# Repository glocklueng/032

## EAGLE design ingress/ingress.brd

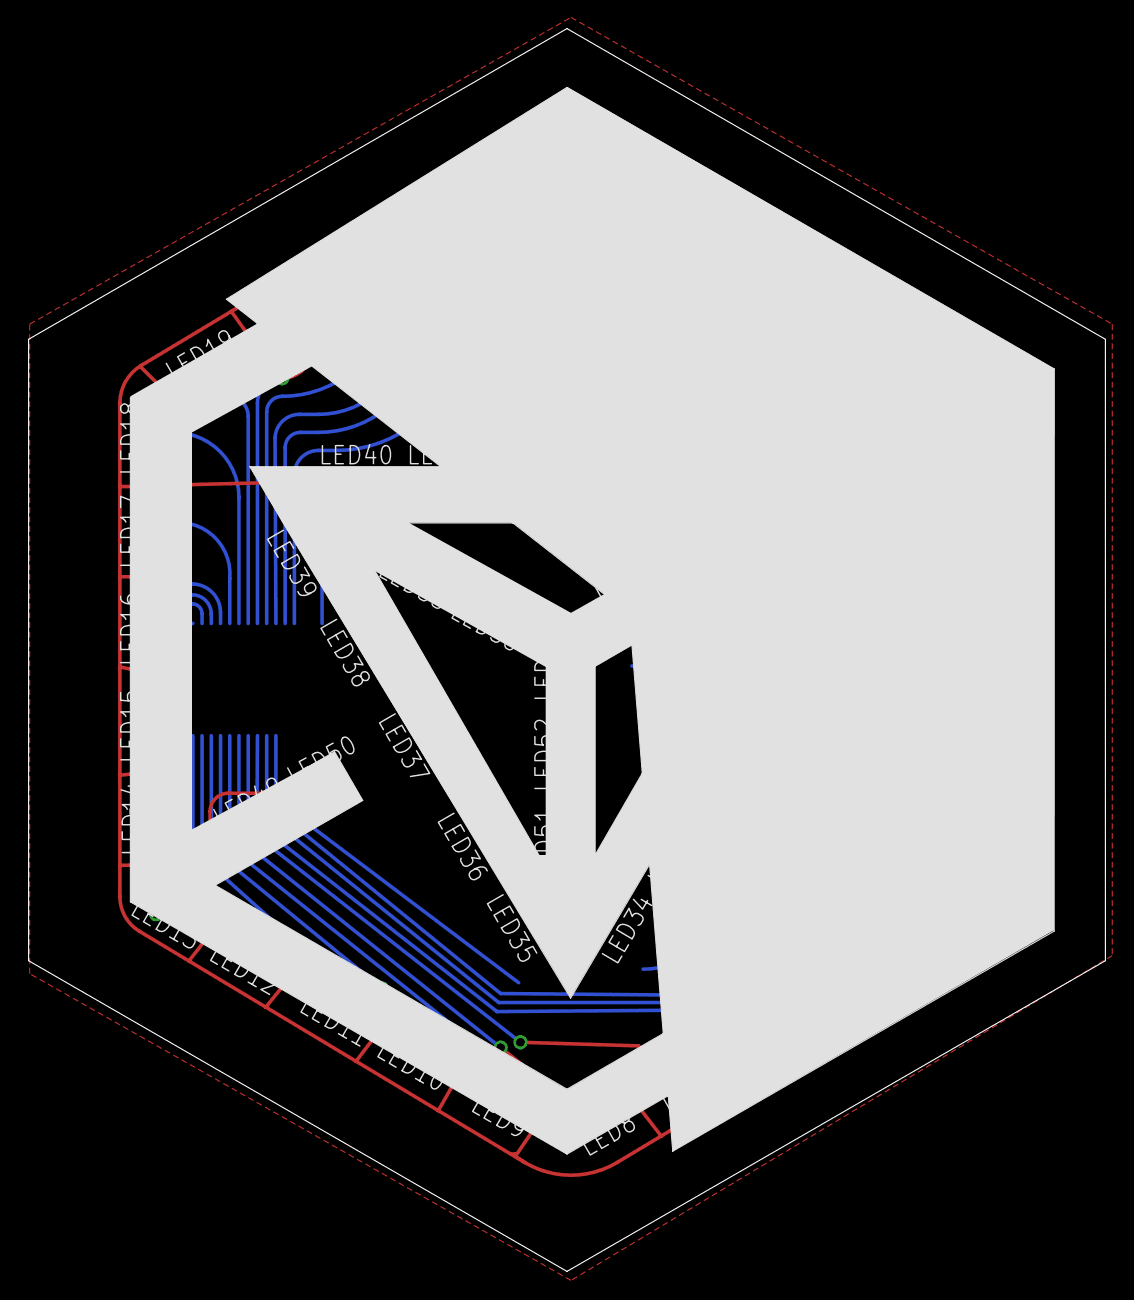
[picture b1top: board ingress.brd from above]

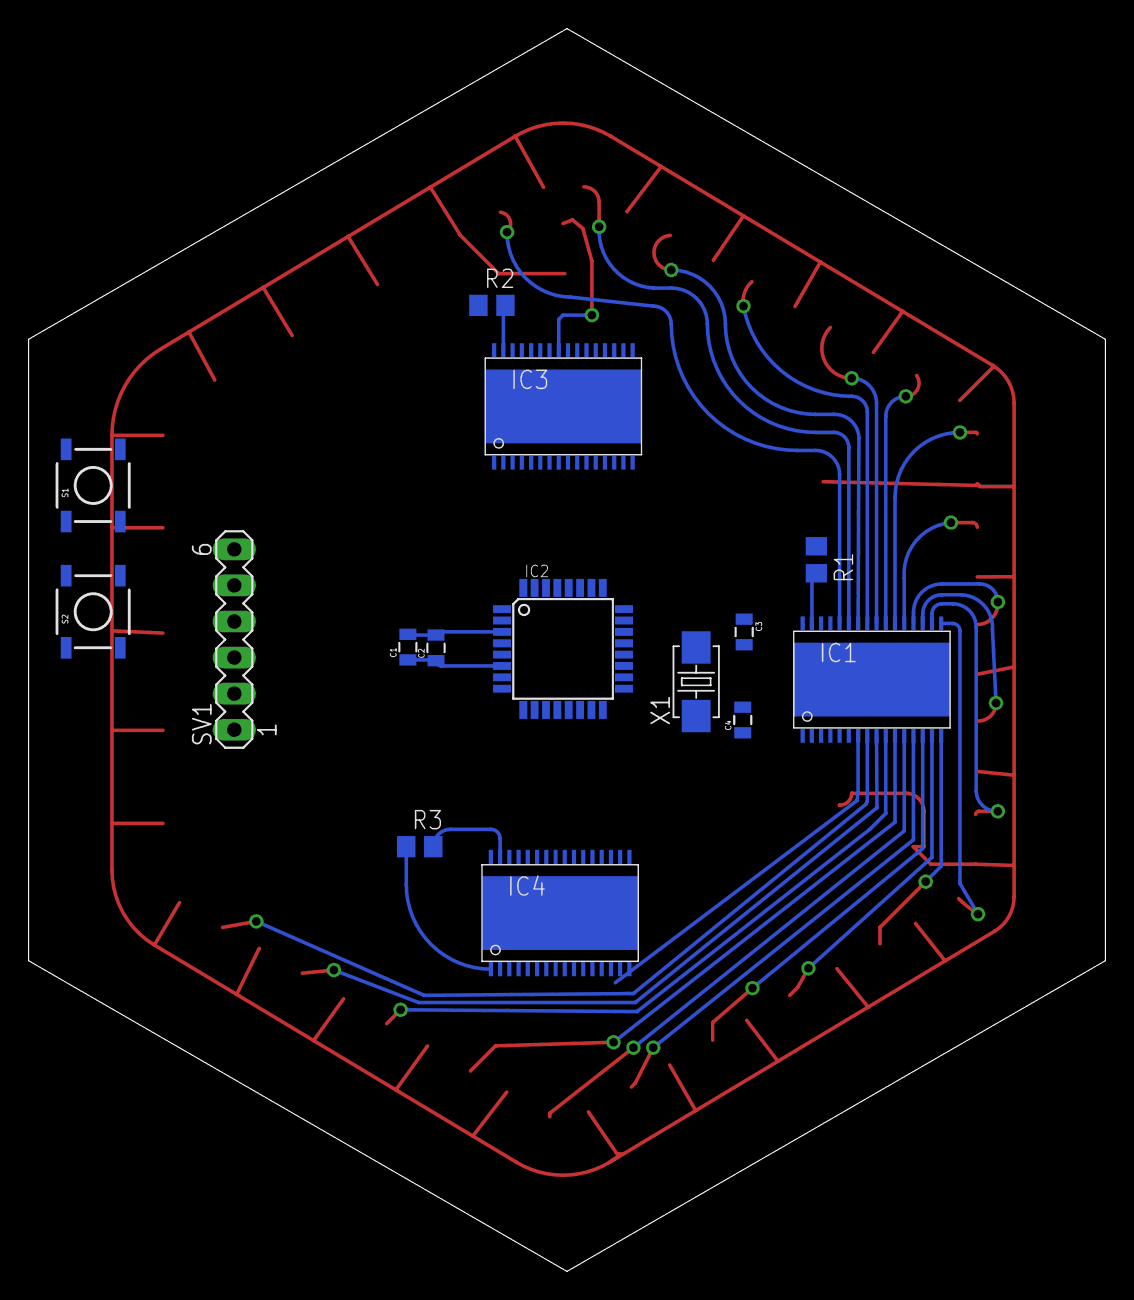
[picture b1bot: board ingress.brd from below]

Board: 2 copper layers, 75.8 x 87.5 mm, 74 parts (15 on the bottom side), 77 nets.

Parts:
C1, C2: .1uF; 0805
C3, C4: 18pF; 0805
IC1: HTSSOP32DAP
IC2: MEGA328-AI; TQFP32-08
IC3, IC4: SLICE_NOSHIFT_TLC5947HTSSOP32DAP; HTSSOP32DAP
LED1, LED2, LED3, LED4, LED5, LED6, LED7, LED8, LED9, LED10, LED11, LED12, LED13, LED14, LED15, LED16, LED17, LED18, LED19, LED20, LED21, LED22, LED23, LED24, LED25, LED26, LED27, LED28, LED29, LED30, LED31, LED32, LED33, LED34, LED35, LED36, LED37, LED38, LED39, LED40, LED41, LED42, LED43, LED44, LED45, LED46, LED47, LED48, LED49, LED50, LED51, LED52, LED53, LED54, LED55, LED56, LED57, LED58, LED59: CHIPLED_1206
R1, R2, R3: 20K; R0805
S1, S2: TACTILE_SWITCH_SMD
SV1: MA06-1
X1: 16Mhz; 5032

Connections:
BLANK: IC1.2, IC2.25, IC3.2, IC4.2
BUTTON: IC2.28, S2.3
COL1: IC1.5, LED1.C
COL2: IC1.6, LED2.C
COL3: IC1.7, LED3.C
COL4: IC1.8, LED4.C
COL5: IC1.9, LED5.C
COL6: IC1.10, LED6.C
COL7: IC1.11, LED7.C
COL8: IC1.12, LED8.C
COL9: IC1.13, LED9.C
COL10: IC1.14, LED10.C
COL11: IC1.15, LED11.C
COL12: IC1.16, LED12.C
COL13: IC1.17, LED13.C
COL14: IC1.18, LED14.C
COL15: IC1.19, LED15.C
COL16: IC1.20, LED16.C
COL17: IC1.21, LED17.C
COL18: IC1.22, LED18.C
COL19: IC1.23, LED19.C
COL20: IC1.24, LED20.C
COL21: IC1.25, LED21.C
COL22: IC1.26, LED22.C
COL23: IC1.27, LED23.C
COL24: IC1.28, LED24.C
COL25: IC3.5, LED25.C
COL26: IC3.6, LED26.C
COL27: IC3.7, LED27.C
COL28: IC3.8, LED28.C
COL29: IC3.9, LED29.C
COL30: IC3.10, LED30.C
COL31: IC3.11, LED31.C
COL32: IC3.12, LED32.C
COL33: IC3.13, LED33.C
COL34: IC3.14, LED34.C
COL35: IC3.15, LED35.C
COL36: IC3.16, LED36.C
COL37: IC3.17, LED37.C
COL38: IC3.18, LED38.C
COL39: IC3.19, LED39.C
COL40: IC3.20, LED40.C
COL41: IC3.21, LED41.C
COL42: IC3.22, LED42.C
COL43: IC3.23, LED43.C
COL44: IC3.24, LED44.C
COL45: IC3.25, LED45.C
COL46: IC3.26, LED46.C
COL47: IC3.27, LED47.C
COL48: IC3.28, LED48.C
COL49: IC4.5, LED49.C
COL50: IC4.6, LED50.C
COL51: IC4.7, LED51.C
COL52: IC4.8, LED52.C
COL53: IC4.9, LED53.C
COL54: IC4.10, LED54.C
COL55: IC4.11, LED55.C
COL56: IC4.12, LED56.C
COL57: IC4.13, LED57.C
COL58: IC4.14, LED58.C
COL59: IC4.15, LED59.C
GND: C1.2, C2.2, C3.2, C4.2, IC1.1, IC2.3, IC2.5, IC2.21, IC3.1, IC4.1, R1.1, R2.1, R3.1, S1.1, S1.2, S2.1, S2.2, SV1.6
MISO: IC2.16, SV1.2
MOSI: IC2.15, SV1.1
unnamed: IC3.31, R2.2
unnamed: C3.1, IC2.7, X1.2
unnamed: C4.1, IC2.8, X1.1
unnamed: IC1.31, R1.2
unnamed: IC4.31, R3.2
RST: IC2.29, S1.3, SV1.5
SCK: IC2.17, SV1.3
SCLK: IC1.3, IC2.24, IC3.3, IC4.3
SIN: IC1.4, IC2.23
SOUT: IC1.29, IC3.4
SOUT_2: IC3.29, IC4.4
VCC: C1.1, C2.1, IC1.32, IC2.4, IC2.6, IC2.18, IC2.20, IC3.32, IC4.32, LED1.A, LED2.A, LED3.A, LED4.A, LED5.A, LED6.A, LED7.A, LED8.A, LED9.A, LED10.A, LED11.A, LED12.A, LED13.A, LED14.A, LED15.A, LED16.A, LED17.A, LED18.A, LED19.A, LED20.A, LED21.A, LED22.A, LED23.A, LED24.A, LED25.A, LED26.A, LED27.A, LED28.A, LED29.A, LED30.A, LED31.A, LED32.A, LED33.A, LED34.A, LED35.A, LED36.A, LED37.A, LED38.A, LED39.A, LED40.A, LED41.A, LED42.A, LED43.A, LED44.A, LED45.A, LED46.A, LED47.A, LED48.A, LED49.A, LED50.A, LED51.A, LED52.A, LED53.A, LED54.A, LED55.A, LED56.A, LED57.A, LED58.A, LED59.A, SV1.4
XLAT: IC1.30, IC2.26, IC3.30, IC4.30

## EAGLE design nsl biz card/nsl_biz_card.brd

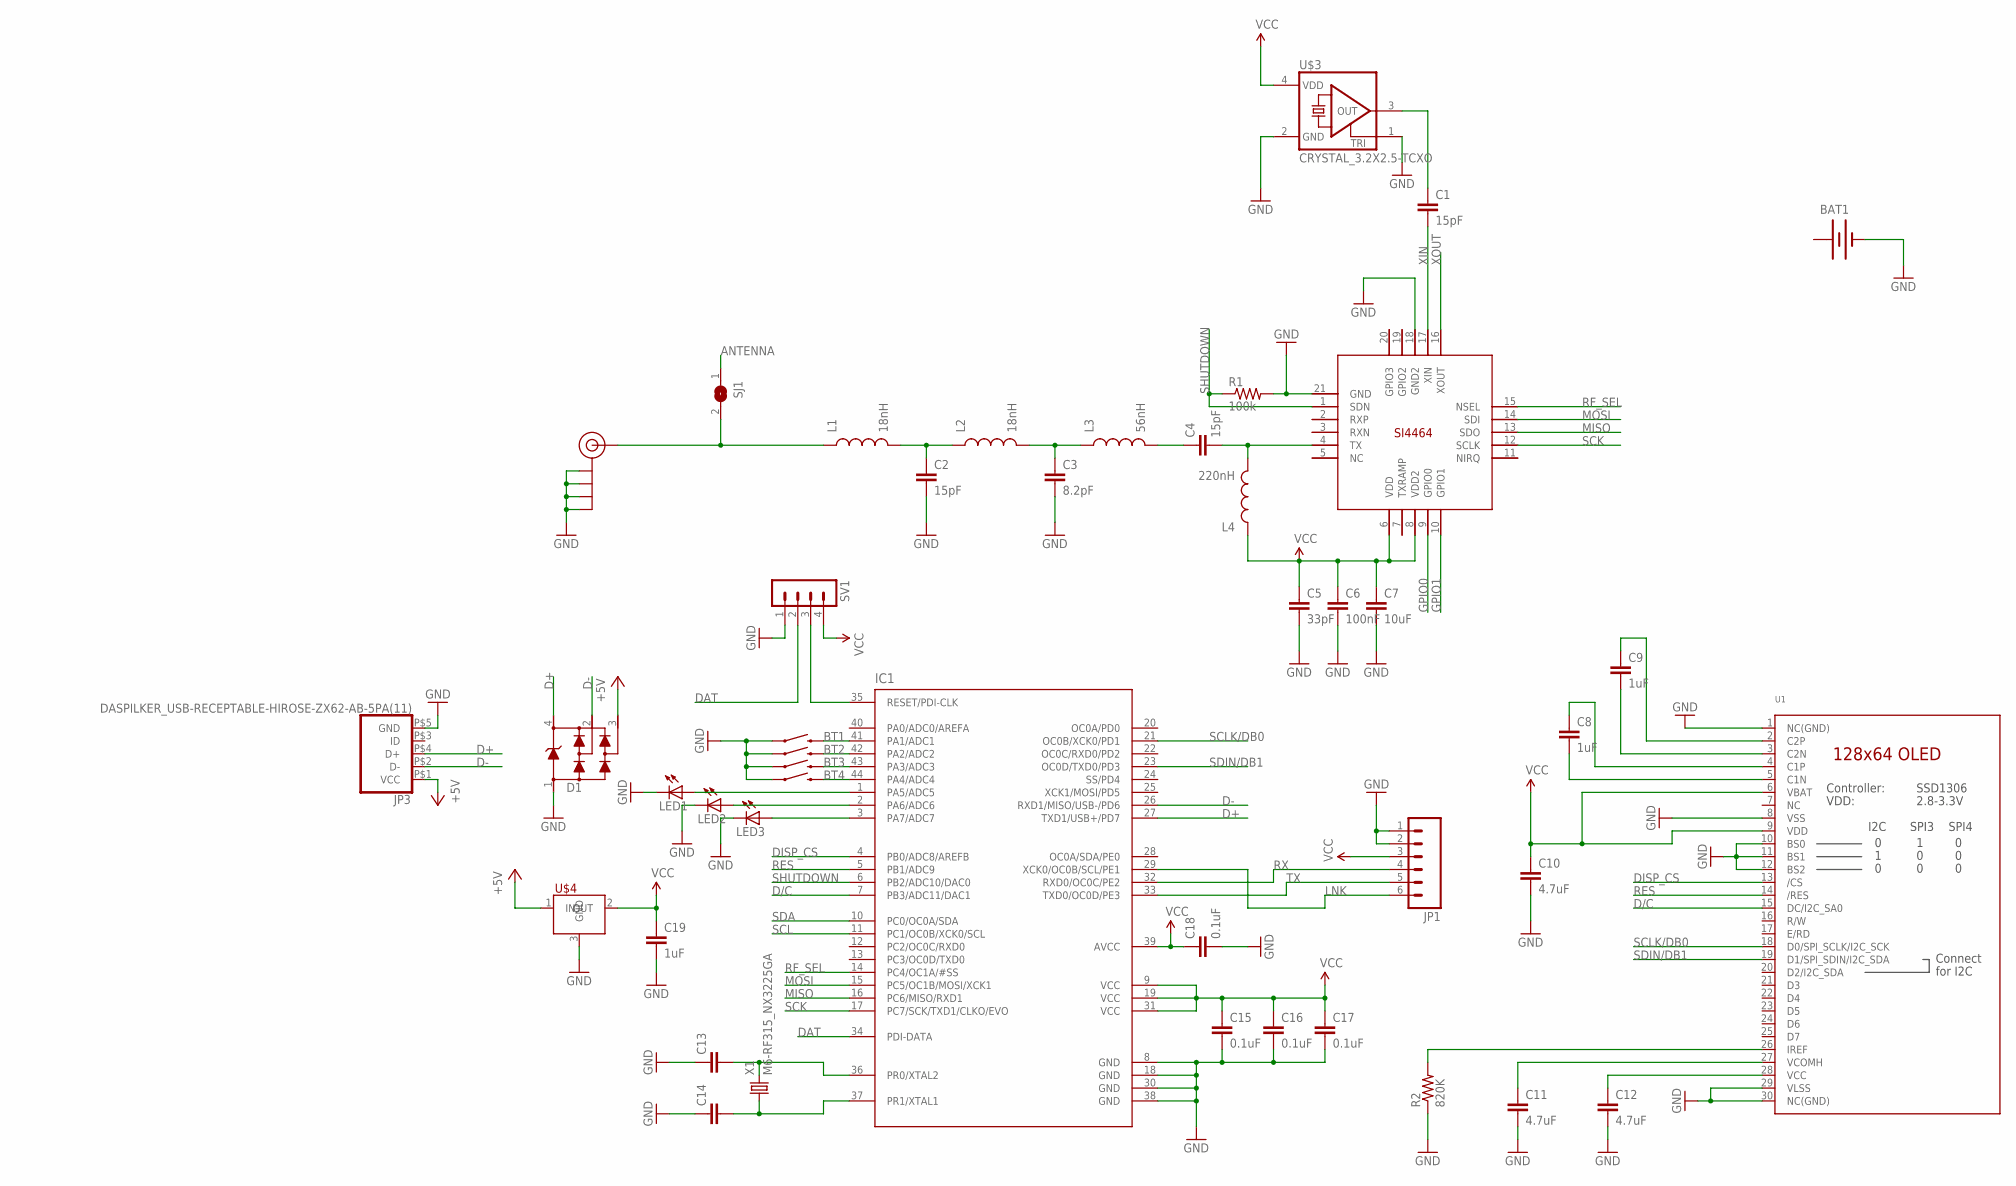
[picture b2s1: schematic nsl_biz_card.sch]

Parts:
BAT1: BATTERY12MM; BATTCON_12MM
C1, C2, C4: 15pF; 0603-CAP
C3: 8.2pF; 0603-CAP
C5: 33pF; 0603-CAP
C6: 100nF; 0603-CAP
C7: 10uF; 0603-CAP
C8, C9: 1uF; 0603-CAP
C10, C11, C12: 4.7uF; 0603-CAP
C13, C14: SPARKFUN_CAP0603-CAP; SPARKFUN_0603-CAP
C15, C16, C17, C18: 0.1uF; SPARKFUN_0603-CAP
C19: 1uF; SPARKFUN_0603-CAP
D1: USBUG_PRTR5V0U2X; USBUG_SOT143B
IC1: OUTLINE_NONOLITH_ATXMEGAXXA4U-AU; OUTLINE_NONOLITH_TQFP-44
J$1: SMA_EDGE; SMA-EDGE
JP1: M06SIP; 1X06
JP3: DASPILKER_USB-RECEPTABLE-HIROSE-ZX62-AB-5PA(11); DASPILKER_HIROSE-ZX62-AB-5PA(11)
L1, L2: 18nH; 0603
L3: 56nH; 0603
L4: 220nH; 0603
LED1, LED2, LED3: LED_LEDCHIP-LED0805; LED_CHIP-LED0805
R1: 100k; 0603-RES
R2: 820K; 0603-RES
S1, S2, S3, S4: SWITCH-MOMENTARY-2; TACTILE_SWITCH_TALL
SJ1: MICROBUILDER_SOLDERJUMPERREFLOW; MICROBUILDER_SOLDERJUMPER_REFLOW
SV1: MA04-1
U1: MICROBUILDER_DISP_OLED_UG-2864HSWEG01; MICROBUILDER_UG-2864HSWEG01_1.3_WRAPAROUND
U$1: SI4464; QFN20+GNDPAD
U$3: CRYSTAL_3.2X2.5-TCXO
U$4: SPARKFUN_AP7333-33SOT23-3; SPARKFUN_SOT23-3
X1: M6-RF315_NX3225GA

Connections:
+: BAT1.PWR@1 (+)
+5V: D1.3, JP3.P$1 (VCC), U$4.1 (IN)
ANTENNA: SJ1.1
BT1: IC1.41 (PA1/ADC1), S4.B2 (2)
BT2: IC1.42 (PA2/ADC2), S3.B2 (2)
BT3: IC1.43 (PA3/ADC3), S2.B2 (2)
BT4: IC1.44 (PA4/ADC4), S1.B2 (2)
D+: D1.4, IC1.27 (TXD1/USB+/PD7), JP3.P$4 (D+)
D-: D1.2, IC1.26 (RXD1/MISO/USB-/PD6), JP3.P$2 (D-)
D/C: IC1.7 (PB3/ADC11/DAC1), U1.15 (DC/I2C_SA0)
DAT: IC1.34 (PDI-DATA), SV1.2
DGND: X1.2 (DGND), X1.4 (DGND)
DISP_CS: IC1.4 (PB0/ADC8/AREFB), U1.13 (/CS)
GND: BAT1.GND (-), C2.2, C3.2, C5.2, C6.2, C7.2, C10.2, C11.2, C12.2, C13.1, C14.1, C15.2, C16.2, C17.2, C18.2, C19.2, D1.1, IC1.8 (GND), IC1.18 (GND), IC1.30 (GND), IC1.38 (GND), J$1.GND@0 (GND), J$1.GND@1 (GND), J$1.GND@2 (GND), J$1.GND@3 (GND), JP1.1, JP1.2, JP3.P$5 (GND), LED1.C, LED2.C, LED3.C, R1.2, R2.1, S1.A2 (1), S2.A2 (1), S3.A2 (1), S4.A2 (1), SV1.1, U1.1 (NC(GND)), U1.8 (VSS), U1.10 (BS0), U1.11 (BS1), U1.12 (BS2), U1.29 (VLSS), U1.30 (NC(GND)), U$1.18 (GND2), U$1.21 (GND), U$3.1 (TRI), U$3.2 (GND), U$4.3 (GND)
GPIO0: U$1.9 (GPIO0)
GPIO1: U$1.10 (GPIO1)
LNK: IC1.29 (XCK0/OC0B/SCL/PE1), JP1.6
MISO: IC1.16 (PC6/MISO/RXD1), U$1.13 (SDO)
MOSI: IC1.15 (PC5/OC1B/MOSI/XCK1), U$1.14 (SDI)
unnamed: C1.1, U$3.3 (OUT)
unnamed: C4.2, L4.2, U$1.4 (TX)
unnamed: C4.1, L3.2
unnamed: C3.1, L2.2, L3.1
unnamed: C2.1, L1.2, L2.1
unnamed: C13.2, IC1.36 (PR0/XTAL2), X1.3 (2)
unnamed: IC1.3 (PA7/ADC7), LED3.A
unnamed: C14.2, IC1.37 (PR1/XTAL1), X1.1
unnamed: IC1.2 (PA6/ADC6), LED2.A
unnamed: IC1.1 (PA5/ADC5), LED1.A
unnamed: C12.1, U1.28 (VCC)
unnamed: IC1.35 (RESET/PDI-CLK), SV1.3
unnamed: C9.1, U1.2 (C2P)
unnamed: C9.2, U1.3 (C2N)
unnamed: C8.1, U1.4 (C1P)
unnamed: C8.2, U1.5 (C1N)
unnamed: C11.1, U1.27 (VCOMH)
unnamed: R2.2, U1.26 (IREF)
unnamed: J$1.SIG (SIGNAL), L1.1, SJ1.2
RES: IC1.5 (PB1/ADC9), U1.14 (/RES)
RF_SEL: IC1.14 (PC4/OC1A/#SS), U$1.15 (NSEL)
RX: IC1.32 (RXD0/OC0C/PE2), JP1.4
SCK: IC1.17 (PC7/SCK/TXD1/CLKO/EVO), U$1.12 (SCLK)
SCL: IC1.11 (PC1/OC0B/XCK0/SCL)
SCLK/DB0: IC1.21 (OC0B/XCK0/PD1), U1.18 (D0/SPI_SCLK/I2C_SCK)
SDA: IC1.10 (PC0/OC0A/SDA)
SDIN/DB1: IC1.23 (OC0D/TXD0/PD3), U1.19 (D1/SPI_SDIN/I2C_SDA)
SHUTDOWN: IC1.6 (PB2/ADC10/DAC0), R1.1, U$1.1 (SDN)
TX: IC1.33 (TXD0/OC0D/PE3), JP1.5
VCC: C5.1, C6.1, C7.1, C10.1, C15.1, C16.1, C17.1, C18.1, C19.1, IC1.9 (VCC), IC1.19 (VCC), IC1.31 (VCC), IC1.39 (AVCC), JP1.3, L4.1, SV1.4, U1.6 (VBAT), U1.9 (VDD), U$1.6 (VDD), U$1.8 (VDD2), U$3.4 (VDD), U$4.2 (OUT)
XIN: C1.2, U$1.17 (XIN)
XOUT: U$1.16 (XOUT)

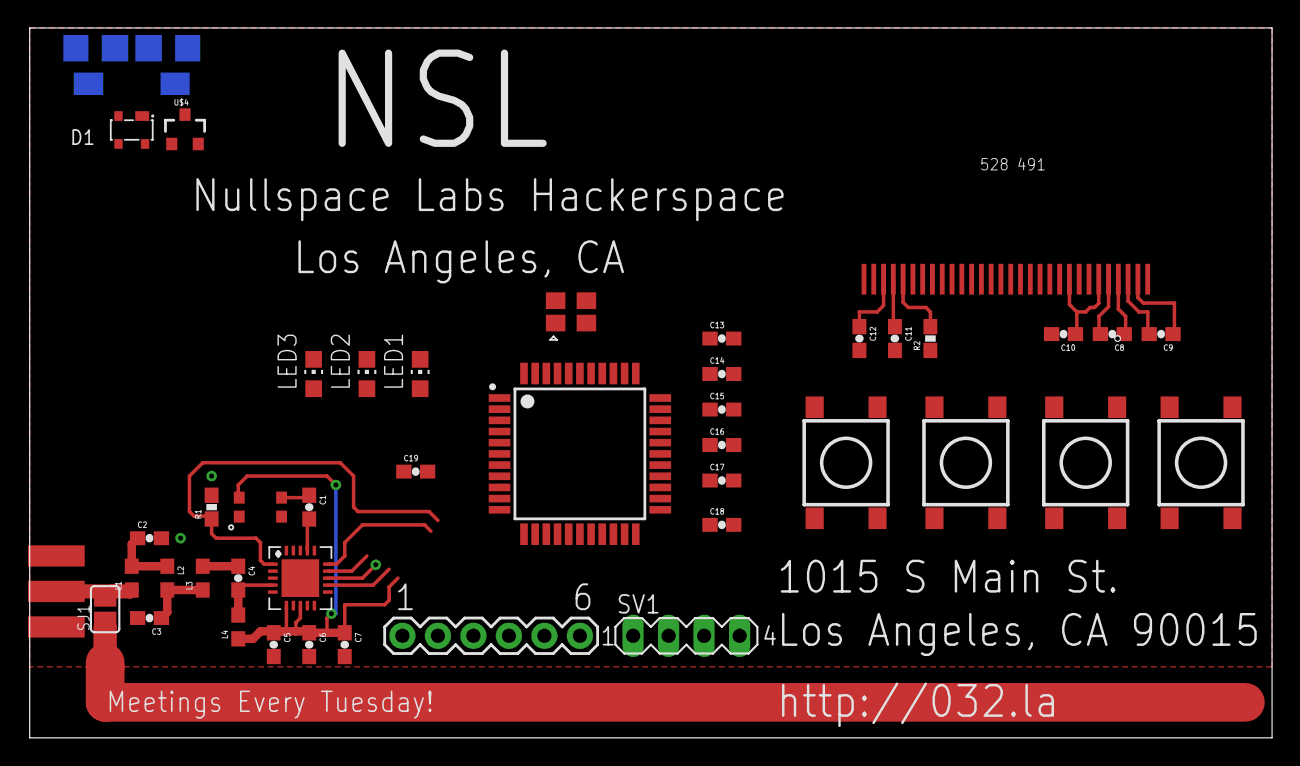
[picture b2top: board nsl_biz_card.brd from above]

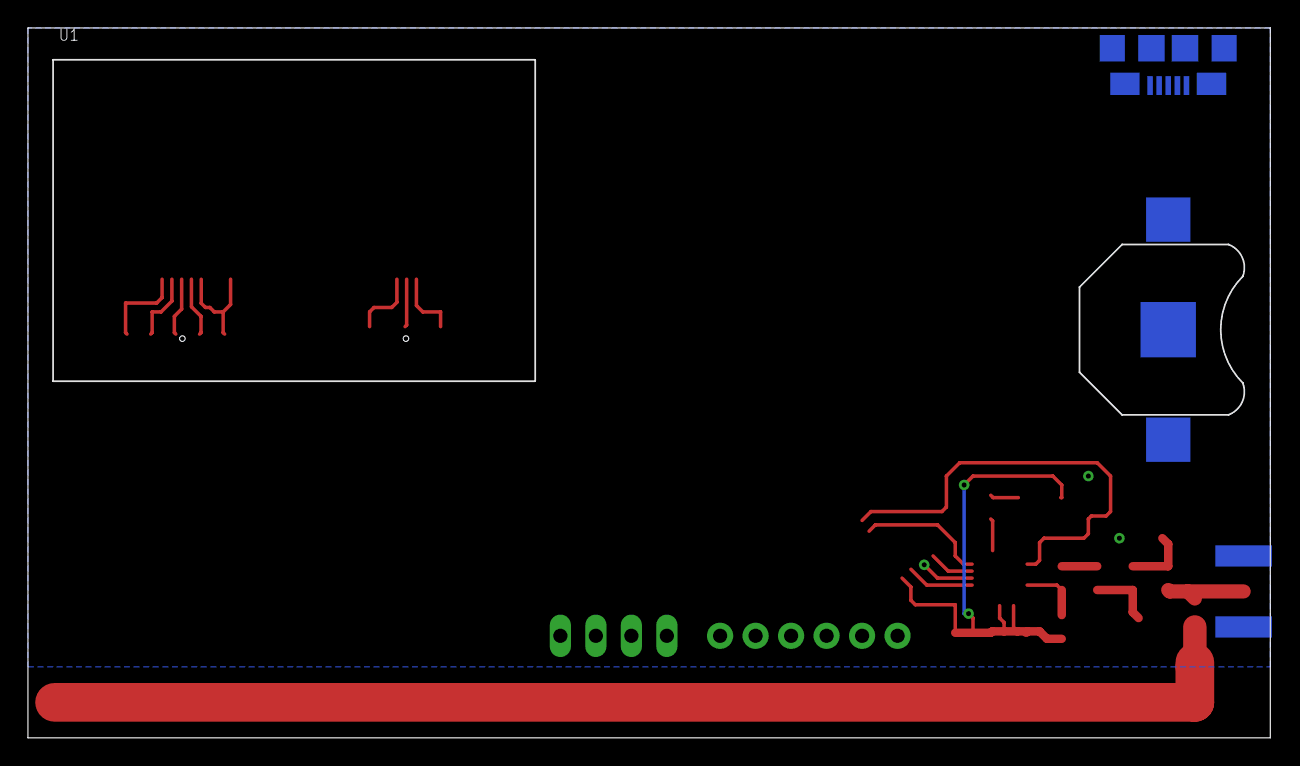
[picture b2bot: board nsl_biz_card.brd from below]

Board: 2 copper layers, 88.9 x 50.8 mm, 45 parts (2 on the bottom side), 44 nets.

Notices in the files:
parts and their libraries:
SparkFun: Licensing: CC v3.0 Share-Alike You are welcome to use this library for commercial purposes.
